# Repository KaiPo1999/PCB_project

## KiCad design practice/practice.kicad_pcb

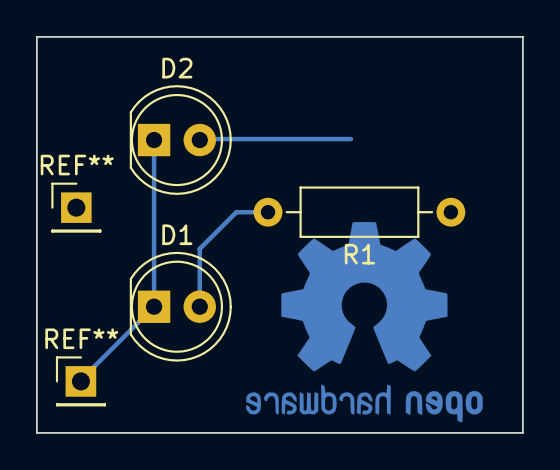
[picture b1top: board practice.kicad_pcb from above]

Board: 2 copper layers, 27.0 x 22.0 mm, 4 parts (1 on the bottom side), 4 nets.

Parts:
D1, D2: LED; LED_D5.0mm
R1: 220; R_Axial_DIN0207_L6.3mm_D2.5mm_P10.16mm_Horizontal
R2: 220; R_0805_2012Metric_Pad1.20x1.40mm_HandSolder

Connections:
GND: R1.1, R2.1
unnamed: D1.2 (A), R1.2
unnamed: D2.2 (A), R2.2
VCC: D1.1 (K), D2.1 (K)

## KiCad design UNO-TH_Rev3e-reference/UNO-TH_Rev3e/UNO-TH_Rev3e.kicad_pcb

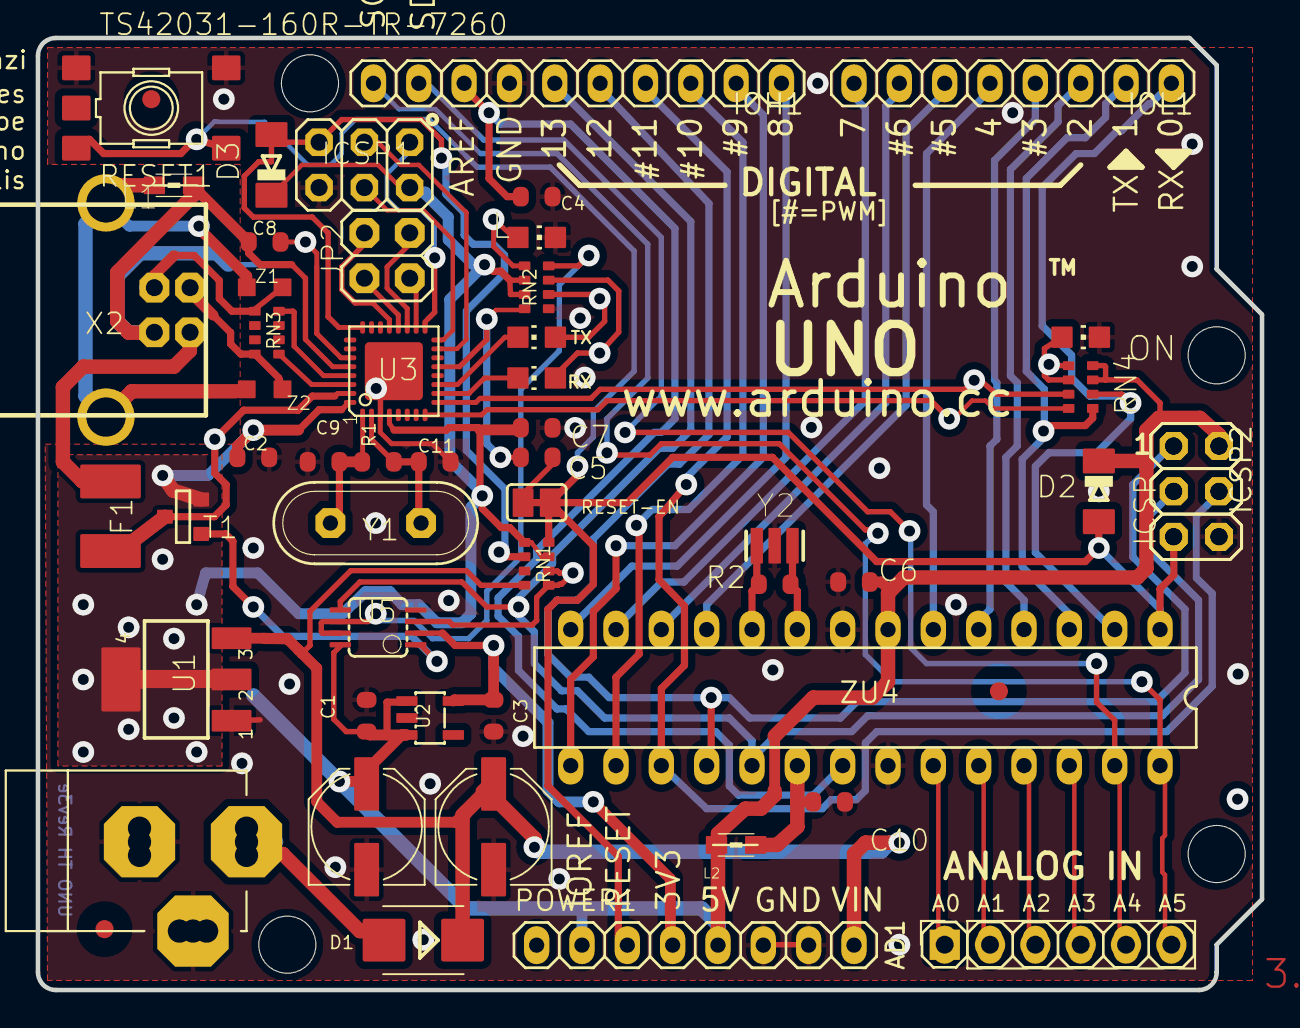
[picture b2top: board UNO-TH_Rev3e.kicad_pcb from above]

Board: 2 copper layers, 68.6 x 53.3 mm, 122 parts (1 on the bottom side), 64 nets.

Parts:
@HOLE0, @HOLE1, @HOLE2, @HOLE3: (no value)
AD: 6x1F-H8.5; 1X06
AD1: 6x1F-H8.5; PinSocket_1x06_P2.54mm_Vertical
C1, C2, C4, C5, C6, C7, C10: 100n; C0603-ROUND
C3, C8: 1u; C0603-ROUND
C9, C11: 22p; C0603-ROUND
D1: M7; SMB
D2, D3: CD1206-S01575; MINIMELF
F1: MF-MSMF050-2 500mA; L1812
FD1, FD2, FD3: FIDUCIALMOUNT; FIDUCIA-MOUNT
FRAME1: DNP; FRAME
GND_TP, GND_TP1: TP_SP; TP-SP
GROUND: SJ
ICSP, ICSP1, ICSP2: 3x2 M; 2X03
IOH1: 10x1F-H8.5; 1X10
IOL1: 8x1F-H8.5; 1X08
JP2: 2x2 M - NM; 2X02
L: YELLOW; CHIP-LED0805
L1: BLM21; 0805
L2: 10uH; 0805
ON: GREEN; CHIP-LED0805
ORIGIN: TP_SP; TP-SP
PC1, PC2: 47u; PANASONIC_D
POWER1: 8x1F-H8.5; 1X08
R1, R2: 1M; R0603-ROUND
RESET1: TS42031-160R-TR-7260; TS42
RESET-EN: SJ
RN1: 10K; CAY16
RN2, RN4: 1K; CAY16
RN3: 22R; CAY16
RX: YELLOW; CHIP-LED0805
T1: FDN340P; SOT-23
TP_0, TP_1, TP_2, TP_3, TP_3V3, TP_4, TP_5, TP_5V, TP_5V1, TP_6, TP_7, TP_8, TP_9, TP_10, TP_11, TP_12, TP_13: TP_SP; TP-SP
TP_A0, TP_A1, TP_A2, TP_A3, TP_A4, TP_A5: TP_SP; TP-SP
TP_AREF: TP_SP; TP-SP
TP_CMP: TP_SP; TP-SP
TP_D+: TP_SP; TP-SP
TP_D-: TP_SP; TP-SP
TP_DTR: TP_SP; TP-SP
TP_GATE: TP_SP; TP-SP
TP_LCMD: TP_SP; TP-SP
TP_LL: TP_SP; TP-SP
TP_MISO2: TP_SP; TP-SP
TP_MOSI2: TP_SP; TP-SP
TP_ONL: TP_SP; TP-SP
TP_PB4, TP_PB5, TP_PB6, TP_PB7: TP_SP; TP-SP
TP_PWRIN: TP_SP; TP-SP
TP_RESET, TP_RESET2: TP_SP; TP-SP
TP_RX: TP_SP; TP-SP
TP_RXL: TP_SP; TP-SP
TP_SCK2: TP_SP; TP-SP
TP_SCL: TP_SP; TP-SP
TP_SDA: TP_SP; TP-SP
TP_TX: TP_SP; TP-SP
TP_TXL: TP_SP; TP-SP
TP_UGND: TP_SP; TP-SP
TP_USBVCC: TP_SP; TP-SP
TP_USH: TP_SP; TP-SP
TP_VIN: TP_SP; TP-SP
TP_VUCAP: TP_SP; TP-SP
TP_XT1, TP_XT2, TP_XT3, TP_XT4: TP_SP; TP-SP
TP_XUSB: TP_SP; TP-SP
TX: YELLOW; CHIP-LED0805
U1: NCP1117ST50T3G; SOT223
U2: LP2985-33DBVR; SOT23-DBV
U3: ATMEGA16U2-MU(R); MLF32
U5: LMV358IDGKR; MSOP08
X1: POWERSUPPLY_DC21MMX; POWERSUPPLY_DC-21MM
X2: USB-B_TH; PN61729
Y1: 16MHz; QS
Y2: CSTCE16M0V53-R0 16MHZ; RESONATOR
Z1, Z2: CG0603MLC-05E; CT_CN0603
ZU4: ATMEGA328P-PU; DIL28-3

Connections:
+5V: C1.2, C2.2, C6.2, C7.1, D2.C, D3.C, ICSP.2, ICSP1.2, ICSP2.2, L2.1, PC2.+, POWER1.2, POWER1.5, RN1.3 (1), RN1.5 (2), RN2.2 (1), RN2.3 (1), RN4.3 (1), RN4.4 (1), T1.2 (S), TP_5V.X, TP_5V1.X (TESTP), U1.2 (OUT@1), U1.4 (OUT), U2.1 (IN), U2.3 (ON/~OFF), U3.4 (VCC), U3.32 (AVCC), U5.8 (V+), ZU4.7 (VCC)
/+3V3: C3.2, POWER1.4, TP_3V3.X (TESTP), U2.5 (OUT), U5.2 (-IN)
/AD0: AD1.1, TP_A0.X (TESTP), ZU4.23 ((ADC0)PC0))
/AD1: AD1.2, TP_A1.X (TESTP), ZU4.24 ((ADC1)PC1)
/AD2: AD1.3, TP_A2.X (TESTP), ZU4.25 ((ADC2)PC2)
/AD3: AD1.4, TP_A3.X (TESTP), ZU4.26 ((ADC3)PC3)
/AD4/SDA: AD1.5, IOH1.9, TP_A4.X (TESTP), ZU4.27 ((ADC4)PC4)
/AD5/SCL: AD1.6, IOH1.10, TP_A5.X (TESTP), ZU4.28 ((ADC5)PC5)
/AREF: C4.2, IOH1.8, ZU4.21 (AREF)
/AVCC: C10.2, L2.2, ZU4.20 (AVCC)
/CMP: RN1.1, RN1.2 (1), U5.3 (+IN)
/D+: RN3.5 (2), X2.3, Z1.1
/D-: RN3.8 (2), X2.2, Z2.1
/DTR: C5.1, RN2.4 (1), U3.13 ((CTS/HWB/AIN6/TO/INT7)PD7)
/GATE_CMD: T1.3 (G), U5.1 (OUT)
/IO0: IOL1.1, RN4.2 (1), TP_0.X (TESTP), ZU4.2 ((RXD)PD0)
/IO1: IOL1.2, RN4.1, TP_1.X (TESTP), ZU4.3 ((TXD)PD1)
/IO2: IOL1.3, TP_2.X (TESTP), ZU4.4 ((INT0)PD2)
/IO3: IOL1.4, TP_3.X (TESTP), ZU4.5 ((INT1)PD3)
/IO4: IOL1.5, TP_4.X (TESTP), ZU4.6 ((T0)PD4)
/IO5: IOL1.6, TP_5.X (TESTP), ZU4.11 ((T1)PD5)
/IO6: IOL1.7, TP_6.X (TESTP), ZU4.12 ((AIN0)PD6)
/IO7: IOL1.8, TP_7.X (TESTP), ZU4.13 ((AIN1)PD7)
/IO8: IOH1.1, TP_8.X (TESTP), ZU4.14 ((ICP)PB0)
/IO9: IOH1.2, TP_9.X (TESTP), ZU4.15 ((OC1)PB1)
/L13: RN2.8 (2), U5.6 (-IN), U5.7 (OUT)
/M8RXD: RN4.7 (2), U3.9 ((TXD1/INT3)PD3)
/M8TXD: RN4.8 (2), U3.8 ((RXD1/AIN1/INT2)PD2)
/MISO: ICSP2.1, IOH1.5, TP_12.X (TESTP), ZU4.18 ((MISO)PB4)
/MISO2: ICSP1.1, TP_MISO2.X (TESTP), U3.17 ((PD0/MISO/PCINT3)PB3)
/MOSI: ICSP2.4, IOH1.4, TP_11.X (TESTP), ZU4.17 ((MOSI)PB3)
/MOSI2: ICSP1.4, TP_MOSI2.X (TESTP), U3.16 ((PDI/MOSI/PCINT2)PB2)
/PB4: JP2.1, TP_PB4.X (TESTP), U3.18 ((T1/PCINT4)PB4)
/PB5: JP2.3, TP_PB5.X (TESTP), U3.19 ((PCINT5)PB5)
/PB6: JP2.2, TP_PB6.X (TESTP), U3.20 ((PCINT6)PB6)
/PB7: JP2.4, TP_PB7.X (TESTP), U3.21 ((PCINT7/OC0A/OC1C)PB7)
/PWRIN: D1.A, X1.2
/RD+: RN3.4 (1), U3.29 (D+)
/RD-: RN3.1, U3.30 (D-)
/RESET: C5.2, D2.A, ICSP2.5, POWER1.3, RESET1.3, RESET1.4, RN1.4 (1), ZU4.1 (RESET)
/RESET2: D3.A, ICSP1.5, RN1.6 (2), TP_RESET2.X (TESTP), U3.24 (RESET(PC1/DW))
/SCK: ICSP2.3, IOH1.6, TP_13.X (TESTP), U5.5 (+IN), ZU4.19 ((SCK)PB5)
/SCK2: ICSP1.3, TP_SCK2.X (TESTP), U3.15 ((SCLK/PCINT1)PB1)
/SS: IOH1.3, TP_10.X (TESTP), ZU4.16 ((SS)PB2)
/TP_VUCAP: C8.1, U3.27 (UCAP)
/UGND: C8.2, L1.1, U3.28 (UGND), X2.4
/USBVCC: F1.1, T1.1 (D), U3.31 (UVCC)
/USHIELD: L1.2, X2.P$1, X2.P$2, Z1.2, Z2.2
/VIN: D1.C, PC1.+, POWER1.8, RN1.8 (2), U1.3 (IN)
/XT1: C9.1, R1.1, TP_XT3.X (TESTP), U3.1 (XTAL1), Y1.2
/XT2: C11.1, R1.2, TP_XT4.X (TESTP), U3.2 (XTAL2(PC0)), Y1.1
/XTAL1: R2.1, TP_XT1.X (TESTP), Y2.3, ZU4.9 (XTAL1)
/XTAL2: R2.2, TP_XT2.X (TESTP), Y2.1, ZU4.10 (XTAL2)
/XUSB: F1.2, X2.1
AD4/SDA: AD.5, TP_SDA.X
AD5/SCL: AD.6, TP_SCL.X
GND: C1.1, C2.1, C3.1, C4.1, C6.1, C7.2, C9.2, C10.1, C11.2, GND_TP.X, GND_TP1.X (TESTP), GROUND.1, ICSP.6, ICSP1.6, ICSP2.6, IOH1.7, L.C, ON.C, PC1.-, PC2.-, POWER1.6, POWER1.7, RESET1.1, RESET1.2, RN1.7 (2), RN2.5 (2), U1.1 (GND/ADJ), U2.2 (GND), U3.3 (GND), U3.33 (PAD), U5.4 (V-), X1.1, X1.3, Y2.2, ZU4.8 (GND), ZU4.22 (AGND)
unnamed: L.A, TP_LL.X
unnamed: ON.A, TP_ONL.X
unnamed: RX.A, TP_RXL.X
unnamed: TP_TXL.X, TX.A
unnamed: RN4.5 (2), RN4.6 (2)
RESET: ICSP.5, RESET-EN.1, RESET-EN.2, TP_RESET.X
UGND: GROUND.2, TP_UGND.X

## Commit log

2022-01-28 2022 01 28 練習
2022-01-29 新增 practice 工程
2022-01-29 修改 R1 阻值
2022-02-06 新增'UNO V3'資料夾 新增'learning project'資料夾
